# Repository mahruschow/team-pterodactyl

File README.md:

# Team PTERODACTYL

Working files for the UMD near-space PTERODACTYL sensor-board redesign. The current board is an imported **v3.8 v11 baseline**, not a completed next-launch design or a fabrication release.

## Team handoff and planning

For a quick picture of progress and what's left, read [docs/REMAINING_WORK.md](docs/REMAINING_WORK.md). Start with [docs/README.md](docs/README.md) for the shared planning directory, then [current status and resume steps](docs/CURRENT_STATUS.md). The directory includes requirements, the development plan, session notes, the supplied parts workbook and native KiCad validation evidence so teammates can continue without the previous chat.

Step 3 now includes a project-local `Pterodactyl_Modules` library with draft BNO055 #2472/MS8607 #4716 carrier footprints with matching symbols, a Teensy SSW carrier, and an unassigned GPS #5440 logical symbol, plus documented connector/mounting proposals. They are not assigned to the main circuit. See [the footprint review](docs/FOOTPRINT_REVIEW.md) for pin mapping, validation and outstanding physical-fit requirements.

Step 5 adds a separate **draft v4 schematic** in `Native_KiCad_v4/`, built from the documented connection map and power architecture. It passes ERC with 0 violations and matches an independent net list, but it is not yet team-reviewed. Step 7 adds a placed (not yet routed) v4 PCB in the same project; see [the draft layout](docs/PCB_LAYOUT_V4.md). See [the power architecture and schematic plan](docs/POWER_ARCHITECTURE.md).

## Open the design

Use KiCad 10 to open `Native_KiCad_v11/PTERODACTYL_v3.8_v11.kicad_pro`. The project contains a native KiCad schematic, PCB, imported symbol and footprint libraries, and project-local library tables. These files were converted from the supplied Autodesk Fusion/Eagle source; component choices and connectivity still need engineering review.

| Folder or file | Purpose |
|---|---|
| `Native_KiCad_v11/` | Editable KiCad project and the saved October 7, 2026 PCB DRC report |
| `Native_KiCad_v4/` | Draft v4 project: schematic (Step 5) and placed, unrouted PCB (Step 7); see docs/PCB_LAYOUT_V4.md |
| `KiCad_import/` | Eagle XML schematic and board pair prepared for KiCad's Eagle importer |
| `Original_Fusion_source/` | Supplied editable `.f3z`, `.sch`, and `.brd` files for comparison |
| `Firmware_v4/` | Draft v4 logger firmware (Step 6); compiles for Teensy 4.1, not yet hardware-tested |
| `Firmware_reference/` | Original v19 and v19.1 firmware archives from the supplied package; not validated for this redesign |
| `Reference_Gerbers_v12_DO_NOT_ORDER/` | Historical Gerbers for revision comparison only |
| `PTERODACTYL_V3.8_Setup_reference.pdf` | Original setup guide from the supplied package |
| `CUSTOM_BOARD_BRIEF.md` | Sensor goals and decisions still to make |

## Current state

The imported PCB has approximately 97.79 × 97.79 mm outer dimensions, four copper layers, 39 footprints, 417 tracks, and two refilled copper zones. It uses a Teensy 4.1 baseline. A fresh KiCad 10.0.7 audit on October 18, 2026 reproduced **11 PCB DRC errors, 428 warnings, and 0 unconnected items**. Schematic ERC reported **33 errors and 10 warnings**, with **52 additional schematic/PCB parity warnings**. These findings remain unresolved. See the [validation report](docs/validation/2026-10-18/VALIDATION_SUMMARY.md) for triage and check limitations, and the [development plan](docs/DEVELOPMENT_PLAN.md) for next steps. The symbols, pin mapping, power architecture and exact module footprints still require engineering review.

The supplied Gerbers say v3.8 **v12** while the editable Fusion source says v3.8 **v11**; the Gerber job metadata also contains a v3.7 identifier. Reconcile those revisions before using any prior files for fabrication.

## Next-launch work

The intended board should log gyroscope, accelerometer, orientation, GPS, pressure, humidity, temperature, and derived altitude data. The working selection is Teensy 4.1 with Adafruit BNO055 2472, MS8607 4716 and PA1616D GPS 5440. The lead has specified no telemetry: record onboard to microSD for analysis after recovery. Saadat selected the core logger with power control, status LEDs and supply monitoring; OLED, remote probes, alternative IMU, heater and servos are outside this scope. Component placement must address interference. Battery/runtime, quantitative performance, enclosure/environment, exact control workflow and manufacturer constraints remain open. See `CUSTOM_BOARD_BRIEF.md` and the [version-one requirements draft](docs/V1_REQUIREMENTS.md), which distinguishes the selected baseline from proposed behavior and open decisions.

Before fabrication: agree on the requirements and reference revision; review the schematic and all footprints against component datasheets; check power, pin mapping, routing, and board dimensions; resolve DRC/ERC failures; generate fresh Gerbers and drill files from the approved KiCad board; inspect them in a Gerber viewer; and obtain a hardware review and prototype test.

## Collaborating

Clone this private repository, open the `.kicad_pro` file, and commit changes on a branch. Keep the KiCad project, schematic, PCB, and local libraries together. Do not commit editor lock files or local UI settings. Explain changes to connectors, sensors, pin mapping, and power in the commit or pull request so they can be checked against the schematic and firmware.

**Do not send the reference Gerbers or this imported baseline directly to a manufacturer.**

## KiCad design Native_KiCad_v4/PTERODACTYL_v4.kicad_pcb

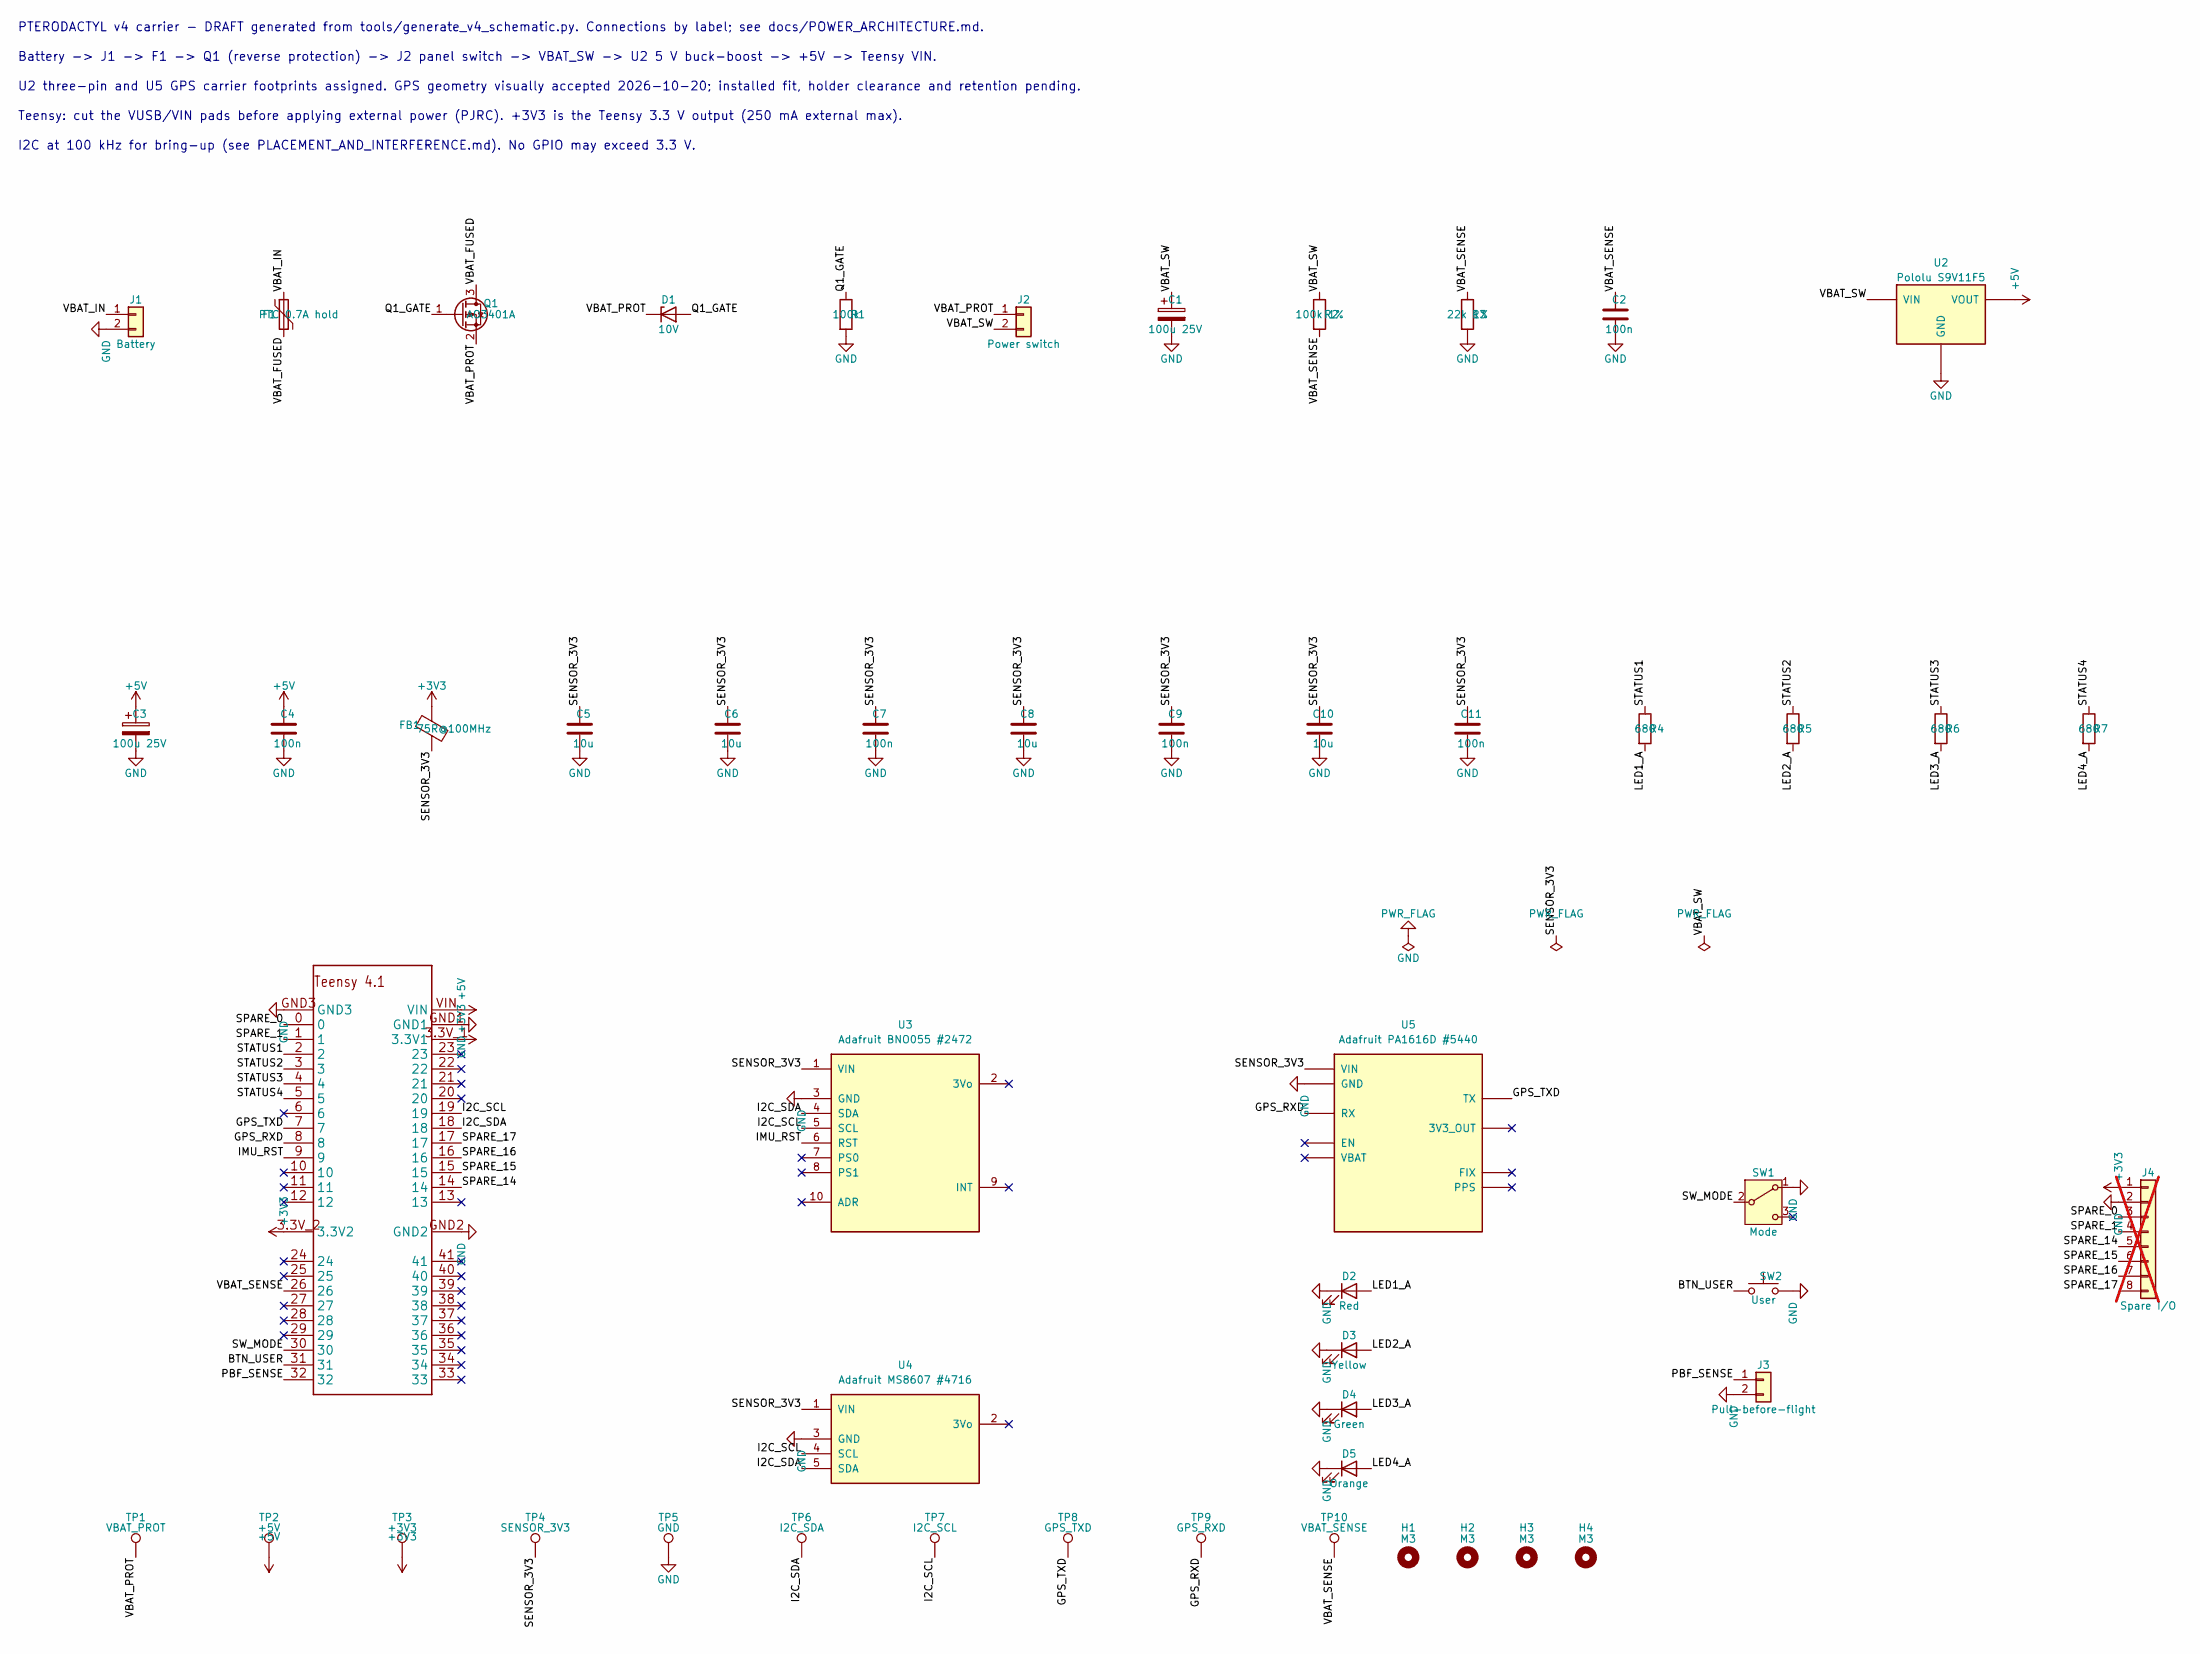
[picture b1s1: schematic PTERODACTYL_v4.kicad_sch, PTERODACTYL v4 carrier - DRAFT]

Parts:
C1, C3: 100u 25V; Panasonic_EEUFR1E101_P2.50mm; MPN EEUFR1E101
C2, C4, C7, C9, C11: 100n; KEMET_C322_100n_P5.00mm; MPN C322C104K5R5TA
C5, C6, C8, C10: 10u; KEMET_C322_10u_P5.00mm; MPN C322C106K3R5TA
D1: 10V; D_DO-35_SOD27_P7.62mm_Horizontal; MPN BZX79-C10,133
D2: Red; LED_D5.0mm; MPN WP7113LID
D3: Yellow; LED_D5.0mm; MPN WP7113LYD
D4: Green; LED_D5.0mm; MPN WP7113LGD
D5: Orange; LED_D5.0mm; MPN WP7113LSECK/J4
F1: PTC 0.7A hold; Fuse_Bourns_MF-RHT070; MPN MF-RHT070-0
FB1: 75R@100MHz; Laird_28L0138_P10.00mm; MPN 28L0138-10R-10
H1, H2, H3, H4: M3; MountingHole_3.2mm_M3
J1: Battery; Molex_0022272021_AISLER; MPN 0022272021
J2: Power switch; Molex_0022272021_AISLER; MPN 0022272021
J3: Pull-before-flight; PinHeader_1x02_P2.54mm_Vertical; MPN HTSW-102-07-T-S
J4: Spare I/O; PinHeader_1x08_P2.54mm_Vertical; MPN DNP; not fitted
Q1: AO3401A; AO3401A_SOT23_AISLER; MPN AO3401A
R1: 100k; Vishay_MRS16_P7.62mm; MPN MRS16000C1003FCT00
R2: 100k 1%; Vishay_MRS16_P7.62mm; MPN MRS16000C1003FCT00
R3: 22k 1%; Vishay_MRS16_P7.62mm; MPN MRS16000C2202FCT00
R4, R5, R6, R7: 680; Vishay_MRS16_P7.62mm; MPN MRS16000C6800FCT00
SW1: Mode; SW_Slide_SPDT_Straight_CK_OS102011MS2Q; MPN OS102011MS2QN1
SW2: User; SW_PUSH_6mm; MPN PTS645SL50-2 LFS
TP1: VBAT_PROT; TestPoint_THTPad_D2.0mm_Drill1.0mm; MPN PCB PAD ONLY
TP2: +5V; TestPoint_THTPad_D2.0mm_Drill1.0mm; MPN PCB PAD ONLY
TP3: +3V3; TestPoint_THTPad_D2.0mm_Drill1.0mm; MPN PCB PAD ONLY
TP4: SENSOR_3V3; TestPoint_THTPad_D2.0mm_Drill1.0mm; MPN PCB PAD ONLY
TP5: GND; TestPoint_THTPad_D2.0mm_Drill1.0mm; MPN PCB PAD ONLY
TP6: I2C_SDA; TestPoint_THTPad_D2.0mm_Drill1.0mm; MPN PCB PAD ONLY
TP7: I2C_SCL; TestPoint_THTPad_D2.0mm_Drill1.0mm; MPN PCB PAD ONLY
TP8: GPS_TXD; TestPoint_THTPad_D2.0mm_Drill1.0mm; MPN PCB PAD ONLY
TP9: GPS_RXD; TestPoint_THTPad_D2.0mm_Drill1.0mm; MPN PCB PAD ONLY
TP10: VBAT_SENSE; TestPoint_THTPad_D2.0mm_Drill1.0mm; MPN PCB PAD ONLY
U1: Teensy 4.1; Teensy41_SSW_Carrier; MPN PJRC Teensy 4.1
U2: Pololu S9V11F5; Pololu_S9V11F5_SSW_Carrier; MPN Pololu #2836
U3: Adafruit BNO055 #2472; Adafruit_BNO055_2472_Carrier; MPN Adafruit 2472
U4: Adafruit MS8607 #4716; Adafruit_MS8607_4716_Carrier; MPN Adafruit 4716
U5: Adafruit PA1616D #5440; Adafruit_GPS_5440_Carrier; MPN Adafruit 5440

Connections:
+3V3: FB1.1, J4.1, TP3.1, U1.3.3V_1 (3.3V1), U1.3.3V_2 (3.3V2)
+5V: C3.1, C4.1, TP2.1, U1.VIN, U2.VOUT
/BTN_USER: SW2.1, U1.31
/GPS_RXD: TP9.1, U1.8, U5.RX
/GPS_TXD: TP8.1, U1.7, U5.TX
/I2C_SCL: TP7.1, U1.19, U3.5 (SCL), U4.4 (SCL)
/I2C_SDA: TP6.1, U1.18, U3.4 (SDA), U4.5 (SDA)
/IMU_RST: U1.9, U3.6 (RST)
/LED1_A: D2.2 (A), R4.2
/LED2_A: D3.2 (A), R5.2
/LED3_A: D4.2 (A), R6.2
/LED4_A: D5.2 (A), R7.2
/PBF_SENSE: J3.1, U1.32
/Q1_GATE: D1.2 (A), Q1.1 (G), R1.1
/SENSOR_3V3: C5.1, C6.1, C7.1, C8.1, C9.1, C10.1, C11.1, FB1.2, TP4.1, U3.1 (VIN), U4.1 (VIN), U5.VIN
/SPARE_0: J4.3, U1.0
/SPARE_1: J4.4, U1.1
/SPARE_14: J4.5, U1.14
/SPARE_15: J4.6, U1.15
/SPARE_16: J4.7, U1.16
/SPARE_17: J4.8, U1.17
/STATUS1: R4.1, U1.2
/STATUS2: R5.1, U1.3
/STATUS3: R6.1, U1.4
/STATUS4: R7.1, U1.5
/SW_MODE: SW1.2 (B), U1.30
/VBAT_FUSED: F1.2, Q1.3 (D)
/VBAT_IN: F1.1, J1.1
/VBAT_PROT: D1.1 (K), J2.1, Q1.2 (S), TP1.1
/VBAT_SENSE: C2.1, R2.2, R3.1, TP10.1, U1.26
/VBAT_SW: C1.1, J2.2, R2.1, U2.VIN
GND: C1.2, C2.2, C3.2, C4.2, C5.2, C6.2, C7.2, C8.2, C9.2, C10.2, C11.2, D2.1 (K), D3.1 (K), D4.1 (K), D5.1 (K), J1.2, J3.2, J4.2, R1.2, R3.2, SW1.1 (A), SW2.2, TP5.1, U1.GND1, U1.GND2, U1.GND3, U2.GND, U3.3 (GND), U4.3 (GND), U5.GND

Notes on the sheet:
PTERODACTYL v4 carrier - DRAFT generated from tools/generate_v4_schematic.py. Connections by label; see docs/POWER_ARCHITECTURE.md.
Battery -> J1 -> F1 -> Q1 (reverse protection) -> J2 panel switch -> VBAT_SW -> U2 5 V buck-boost -> +5V -> Teensy VIN.
U2 three-pin and U5 GPS carrier footprints assigned. GPS geometry visually accepted 2026-10-20; installed fit, holder clearance and retention pending.
Teensy: cut the VUSB/VIN pads before applying external power (PJRC). +3V3 is the Teensy 3.3 V output (250 mA external max).
I2C at 100 kHz for bring-up (see PLACEMENT_AND_INTERFERENCE.md). No GPIO may exceed 3.3 V.

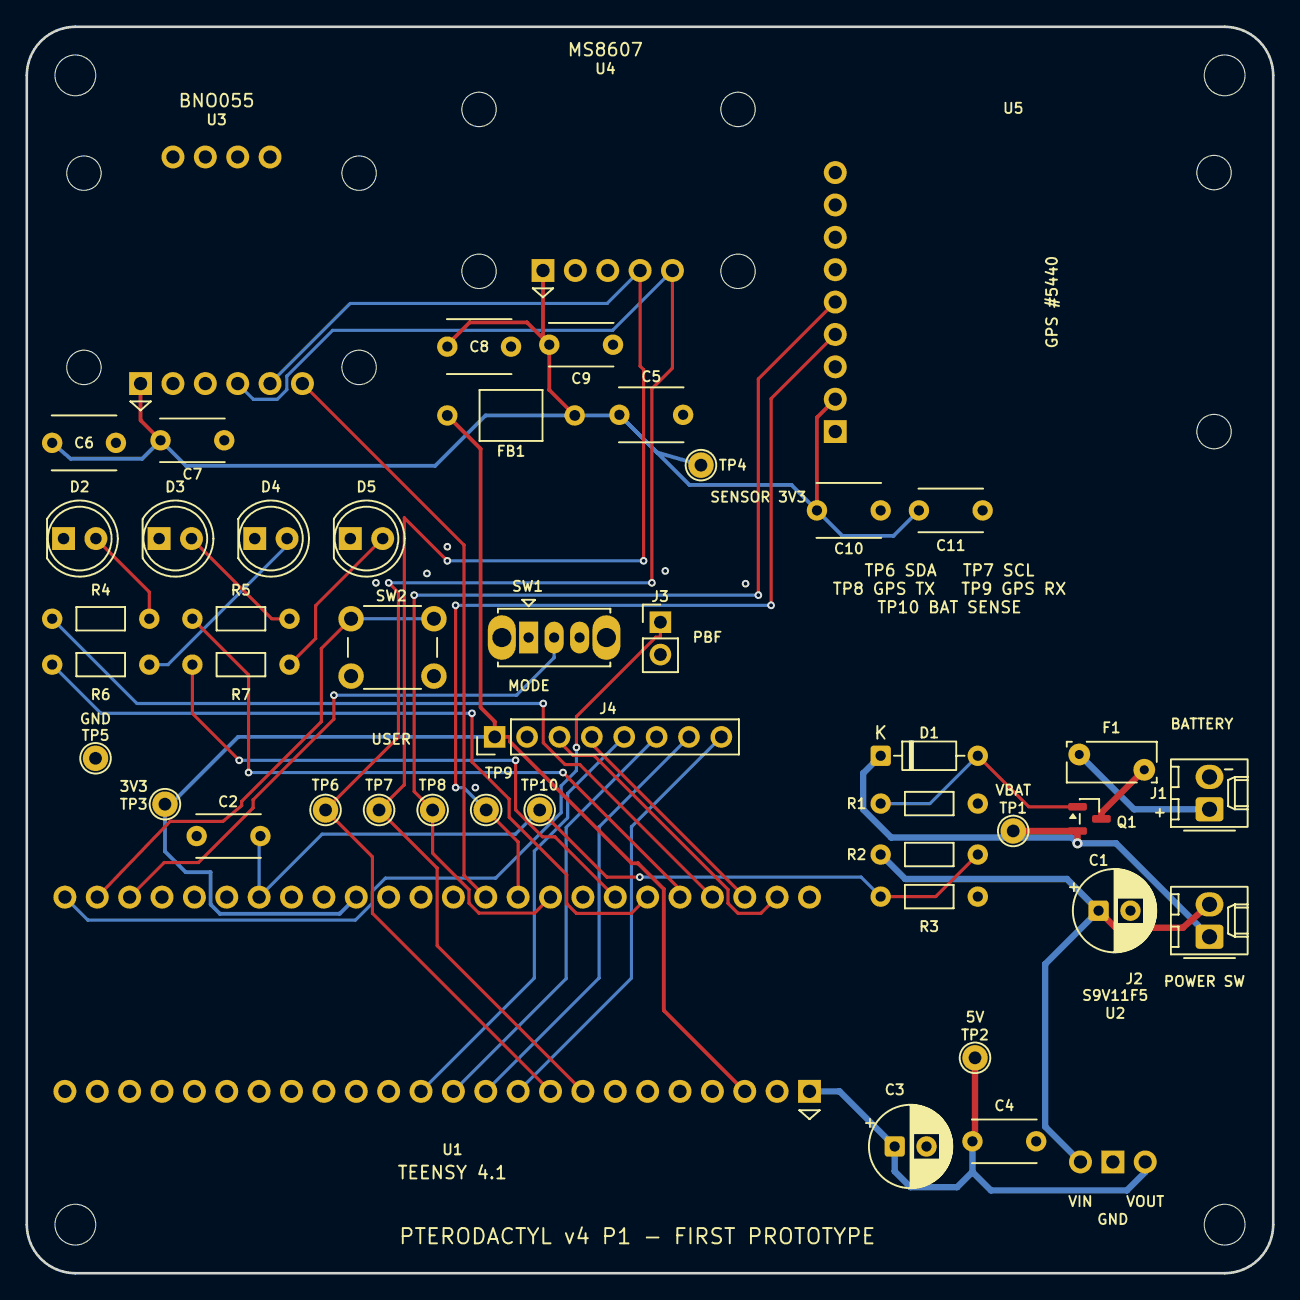
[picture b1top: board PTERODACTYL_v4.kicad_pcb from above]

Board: 4 copper layers, 97.8 x 97.8 mm, 51 parts (0 on the bottom side), 32 nets.

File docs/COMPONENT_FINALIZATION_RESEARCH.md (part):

# Component finalization research — handoff October 21, 2026

## Team-name silkscreen update — October 21, 2026

Saadat Muyeen, Mahrus Chowdhury and Ryeed Zaman are now on the back silkscreen, with 2 mm text and 0.30 mm strokes. Fresh DRC, connectivity and schematic-parity checks report zero issues. All original PCB bytes are retained; only three text objects were added. The other eight Gerber layers match the prior geometry exactly, apart from export timestamps. Existing ERC evidence remains applicable to the unchanged schematic.

**Order the updated native PCB or fabrication ZIP. AISLER TCVOYNZG revision 1 is superseded and does not contain the names.** Two revision-upload attempts failed; the alternate upload form says an anonymous project is already in progress and requires login to save it. Sign in and upload the updated board, then inspect the bottom preview before ordering. No new AISLER revision or order has been created. Earlier statements below about revision 1 being the exact current PCB or ready for checkout refer to the previous checkpoint.

## First prototype scope and order checkpoint - October 21, 2026

**Current authority: [FIRST_PROTOTYPE_RELEASE.md](FIRST_PROTOTYPE_RELEASE.md).** PCB checks and AISLER upload/preview passed; project TCVOYNZG revision 1 is ready for checkout. FB1/SW1/SW2/J3 are selected for P1. The user explicitly excludes physical testing, flight qualification, subsequent redesign and casing from this phase; older statements requiring those before PCB fabrication are superseded. Assembly receipt/polarity checks remain part of building the prototype. No order placed. Updated known cost is USD 129.37 (15 price lines missing); entered mass 170.25 g (three missing). The provisional EUR board quote is separate.

**Historical research checkpoint, not a released BOM.** The later targeted implementation and revised choices (including MRS16 and BH4AAW) are in [COMPONENT_IMPLEMENTATION.md](COMPONENT_IMPLEMENTATION.md). Statements below about changes not being applied describe the earlier checkpoint.

**Original research boundary:** These recommendations have not been applied to the schematic, PCB, exported BOM or live budget. The current native design still contains the earlier candidate/generic components. See RESUME_HERE.md for authoritative requirements and next actions. No purchase or new native-design validation occurred during this research.

## Battery and storage recommendations

**Battery: four Energizer L91 AA Li/FeS2 primary cells in series**, nominal 6 V, typical cell-only mass 60 g. This is the leading lightweight candidate for the existing buck-boost architecture, not a guarantee of three-hour operation. Its published operating range includes -40 C. Four cells reduce required current and improve startup voltage margin relative to three; series connection does not multiply Ah. These are non-rechargeable cells. [Energizer current datasheet](https://data.energizer.com/pdfs/L91GL0225.pdf).

The manufacturer's temperature graph was visually inspected: capacity falls strongly at -40 C under higher loads. The 2.5 A continuous headline is single-cell data at room temperature unless otherwise stated; do not apply it unchanged at -40 C. Do not assign a fixed 3.5 Ah cold capacity from the room-temperature curve. Existing model currents for a four-cell pack are approximately 0.249 A average / 0.547 A peak at 6 V, and 0.374 A / 0.821 A at 4 V. Four volts is a screening example, not an implemented cutoff. The regulator needs at least 3 V at its own input to start, after wiring/protection losses. Select a qualified loaded-voltage endpoint and test cold startup and complete logging.

The **holder/finished pack is unresolved**. MPD BA4AAW's manufacturer drawing specifies -10 to +100 C, so it is not an acceptable rated -40 C choice. MPD 6S-AA is rated -40 to +180 C but holds only ONE cell and uses PCB pins; four of them would need additional integration. Do not misidentify it as a four-cell holder. A professionally assembled pack is another option, but no pack-builder SKU has been verified. Cell restraint, wiring and connector mass must be added to the 60 g cells. Sources: [BA4AAW drawing](https://www.batteryholders.com/uploads/parts/BA4AAW/datashee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, [MPD 6S-AA](https://products.memoryprotectiondevices.com/?page_id=793).

**microSD: Kingston Industrial SDCIT2/8GB**, 8 GB pSLC industrial microSDHC, -40 to +85 C; FAT32 for the initial Teensy logging setup. SDCIT2/8GBSP is the no-adapter variant; the adapter is not flown. Eight GB leaves ample space for this logger. The public summary does not establish an exact current maximum; measure write/startup peaks and retain an explicitly provisional allowance. Card power-failure features do not replace firmware sync/clean-stop handling. [Kingston datasheet](https://www.kingston.com/datasheets/SDCIT2_en.pdf), [exact product](https://www.kingston.com/en/memory/search?partid=SDCIT2%2F8GB).

## On-board component research

The table records the proposed order code and remaining review, not permission to silently substitute other parts. Quantities derive from the current schematic.

| References | Proposed exact part | Findings / remaining work |
| --- | --- | --- |
| U1–U5 | PJRC Teensy 4.1; Pololu 2836; Adafruit 2472, 4716, 5440 | Retain specified modules. Whole-module cold operation is not established merely from individual IC ratings. |
| C1, C3 | Panasonic **EEUFR1E101**, 100 uF 25 V | Proposed C1 increase from 47 to 100 uF and C3 voltage increase from 10 to 25 V. 6.3 mm diameter, 11.2 mm body length, 2.5 mm pitch, -40 to +105 C. Existing radial footprint matches nominal pitch/diameter; height and cold impedance still need review. |
| C2, C4, C7, C9, C11 | KEMET **C322C104K5R5TA**, 100 nF 50 V 10% X7R | Max body 5.08 mm long, 3.18 mm thick, 6.6 mm high. Generic disc body is inaccurate. |
| C5, C6, C8, C10 | KEMET **C322C106K3R5TA**, 10 uF 25 V 10% X7R | Max body 5.08 mm long, 4.07 mm thick, 6.6 mm high. Generic disc body is inaccurate. Review usable capacitance under bias and temperature. |
| Q1 | Alpha & Omega **AO3401A** | Candidate replacement for discontinued IRLML6402. SOT-23 G/S/D, top-view drawing inspected. -30 V Vds, +/-12 V Vgs, max 85 mOhm at -2.5 V gate drive. Check pin mapping against existing G1/S2/D3 and source-to-protected-rail orientation. No replacement applied yet. |
| D1 | Nexperia **BZX79-C10,133** | 10 V zener, DO-35. Existing R1 gives low clamp bias; do not claim precise 10 V clamping at arbitrary input voltage. Four-cell battery contract is narrower than regulator's standalone 16 V input limit. |
| F1 | Bourns **MF-RHT070-0** | 0.7 A hold / 1.4 A trip nominal at 23 C. Hold changes with temperature (about 0.95 A at -40 C, 0.62 A at 40 C). Review time-current curve, path loss, startup and fault behavior; hold is not an instantaneous cutoff. Retain as candidate until reviewed. |
| FB1 | Murata **BL01RN1A2A2B** | Bulk packaging suffix B; source family drawing matches existing axial footprint. Confirm exact current, temperature and ordering status from manufacturer documentation before closing. |
| R1, R2 | Vishay **MRS25000C1003FCT00** | 100 kOhm, 1%. Check active ordering status and maximum body dimensions against DIN0207 footprint. |
| R3 | Vishay **MRS25000C2202FCT00** | 22 kOhm, 1%. Same family review. |
| R4–R7 | Vishay **MRS25000C6800FCT00** | 680 Ohm, 1%. Retain resistance. |
| D2 | Kingbright **WP7113LID** | Low-current red, 5 mm THT. |
| D3 | Kingbright **WP7113LYD** | Low-current yellow, 5 mm THT. |
| D4 | Kingbright **WP7113LGD** | Low-forward-voltage green, 5 mm THT; avoid a generic high-Vf green substitution. |
| D5 | Kingbright **WP7113LSECK/J4** | Low-current orange, 5 mm THT. Check flange/body limits and recalculate actual LED current assumptions. |
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
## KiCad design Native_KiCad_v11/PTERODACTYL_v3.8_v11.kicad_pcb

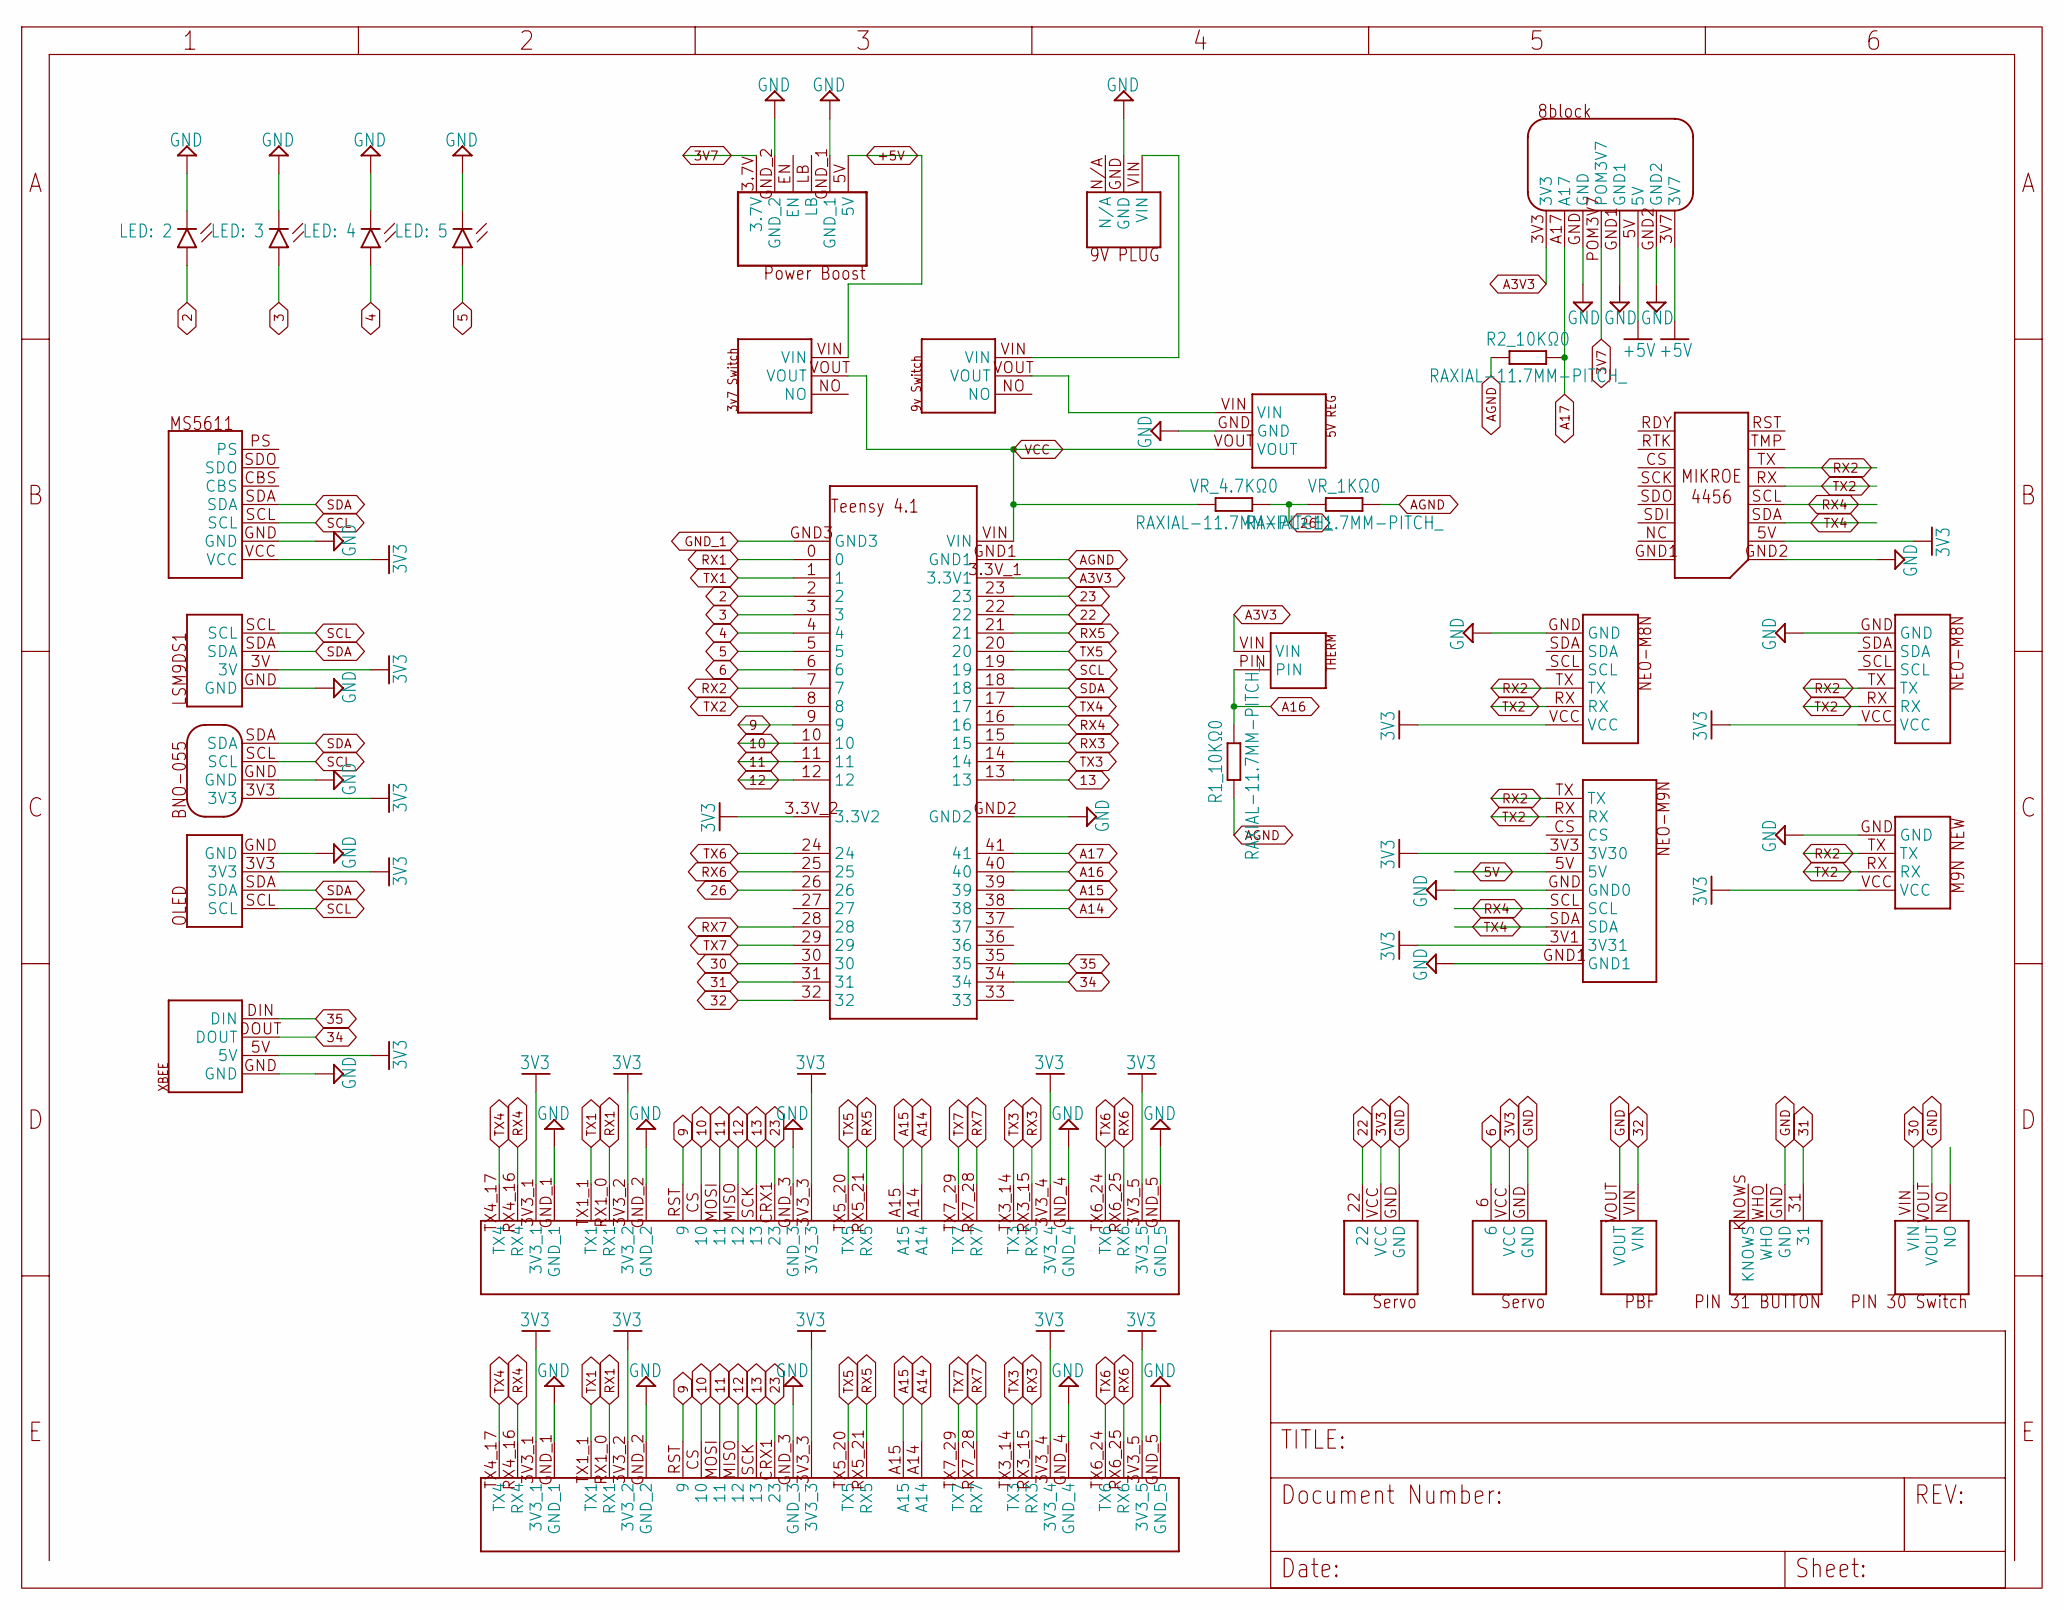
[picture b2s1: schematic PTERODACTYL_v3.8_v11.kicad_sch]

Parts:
D1: LED: 3; LEDRD254W60D565H860B_W
D2: LED: 4; LEDRD254W60D565H860B
D3: LED: 5; LEDRD254W60D565H860B_B
D4: LED: 2; LEDRD254W60D565H860B_Y
R1_10KΩ0, R2_10KΩ0: RAXIAL-11.7MM-PITCH_; RESAD1176W63L850D250B
U$1: FEMALE_HEADERS_V1.3
U$2: TERMINAL_BLOCK_V1.3
U$3: TEENSY41_SIMPLE
U$4: PT8BLOCK; PTERODACTYL8BLOCK
U$5: 5VREG
U$6: 3V7SWITCH
U$7: 9VSWITCH
U$8: 9VPLUG
U$9: OLED_SIMPLE
U$10: LSM9DS1_SIMPLE
U$11: MS5611
U$12: UBLOXM8NTERMINAL
U$13: UBLOXM8NSIMPLE
U$14: XBEE_SIMPLE
U$15: UBLOXM9NSIMPLE
U$16: THERMISTOR10K1; THERMISTOR10K
U$17: BNO055
U$22: UBLOXM9N_NEW_SIMPLE
U$23: SERVO; PIN6SERVO
U$24: PBF; PULLBEFOREFLIGHT
U$25: BUTTON; PIN31BUTTON
U$26: PIN30SWITCH
U$27: SERVO22; PI22SERVO
U$28: POWERBOOST; 5VPOWERBOOST
U$29: MIKROE
VR_1KΩ0, VR_4.7KΩ0: RAXIAL-11.7MM-PITCH_; RESAD1176W63L850D250B

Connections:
2: D4.1 (A), U$3.2
3: D1.1 (A), U$3.3
3V3: U$1.3V3_1, U$1.3V3_2, U$1.3V3_3, U$1.3V3_4, U$1.3V3_5, U$2.3V3_1, U$2.3V3_2, U$2.3V3_3, U$2.3V3_4, U$2.3V3_5, U$3.3.3V_2 (3.3V2), U$9.3V3, U$10.3V, U$11.VCC, U$12.VCC, U$13.VCC, U$14.5V, U$15.3V1 (3V31), U$15.3V3 (3V30), U$17.3V3, U$22.VCC, U$23.VCC, U$27.VCC, U$29.5V
3V7: U$4.POM3V7, U$28.3.7V
4: D2.1 (A), U$3.4
5: D3.1 (A), U$3.5
5V: U$15.5V
6: U$3.6, U$23.6
9: U$1.RST (9), U$2.RST (9), U$3.9
10: U$1.CS (10), U$2.CS (10), U$3.10
11: U$1.MOSI (11), U$2.MOSI (11), U$3.11
12: U$1.MISO (12), U$2.MISO (12), U$3.12
13: U$1.SCK (13), U$2.SCK (13), U$3.13
22: U$3.22, U$27.22
23: U$1.CRX1 (23), U$2.CRX1 (23), U$3.23
26: U$3.26, VR_1KΩ0.1, VR_4.7KΩ0.2
30: U$3.30, U$26.VIN
31: U$3.31, U$25.31
32: U$3.32, U$24.VIN
34: U$3.34, U$14.DOUT
35: U$3.35, U$14.DIN
+5V: U$4.3V7, U$4.5V, U$6.VIN, U$28.5V
A3V3: U$3.3.3V_1 (3.3V1), U$4.3V3, U$16.VIN
A14: U$1.A14, U$2.A14, U$3.38
A15: U$1.A15, U$2.A15, U$3.39
A16: R1_10KΩ0.2, U$3.40, U$16.PIN
A17: R2_10KΩ0.2, U$3.41, U$4.A17
AGND: R1_10KΩ0.1, R2_10KΩ0.1, U$3.GND1, VR_1KΩ0.2
GND: D1.2 (C), D2.2 (C), D3.2 (C), D4.2 (C), U$1.GND_1, U$1.GND_2, U$1.GND_3, U$1.GND_4, U$1.GND_5, U$2.GND_1, U$2.GND_2, U$2.GND_3, U$2.GND_4, U$2.GND_5, U$3.GND2, U$4.GND, U$4.GND1, U$4.GND2, U$5.GND, U$8.GND, U$9.GND, U$10.GND, U$11.GND, U$12.GND, U$13.GND, U$14.GND, U$15.GND (GND0), U$15.GND1, U$17.GND, U$22.GND, U$23.GND, U$24.VOUT, U$25.GND, U$26.VOUT, U$27.GND, U$28.GND_1, U$28.GND_2, U$29.GND2
GND_1: U$3.GND3
RX1: U$1.RX1_0 (RX1), U$2.RX1_0 (RX1), U$3.0
RX2: U$3.7, U$12.TX, U$13.TX, U$15.TX, U$22.TX, U$29.TX
RX3: U$1.RX3_15 (RX3), U$2.RX3_15 (RX3), U$3.15
RX4: U$1.RX4_16 (RX4), U$2.RX4_16 (RX4), U$3.16, U$15.SCL, U$29.SCL
RX5: U$1.RX5_21 (RX5), U$2.RX5_21 (RX5), U$3.21
RX6: U$1.RX6_25 (RX6), U$2.RX6_25 (RX6), U$3.25
RX7: U$1.RX7_28 (RX7), U$2.RX7_28 (RX7), U$3.28
SCL: U$3.19, U$9.SCL, U$10.SCL, U$11.SCL, U$17.SCL
SDA: U$3.18, U$9.SDA, U$10.SDA, U$11.SDA, U$17.SDA
TX1: U$1.TX1_1 (TX1), U$2.TX1_1 (TX1), U$3.1
TX2: U$3.8, U$12.RX, U$13.RX, U$15.RX, U$22.RX, U$29.RX
TX3: U$1.TX3_14 (TX3), U$2.TX3_14 (TX3), U$3.14
TX4: U$1.TX4_17 (TX4), U$2.TX4_17 (TX4), U$3.17, U$15.SDA, U$29.SDA
TX5: U$1.TX5_20 (TX5), U$2.TX5_20 (TX5), U$3.20
TX6: U$1.TX6_24 (TX6), U$2.TX6_24 (TX6), U$3.24
TX7: U$1.TX7_29 (TX7), U$2.TX7_29 (TX7), U$3.29
VCC: U$3.VIN, U$5.VOUT, U$6.VOUT, VR_4.7KΩ0.1
VCC_2: U$7.VIN, U$8.VIN
VCC_3: U$5.VIN, U$7.VOUT

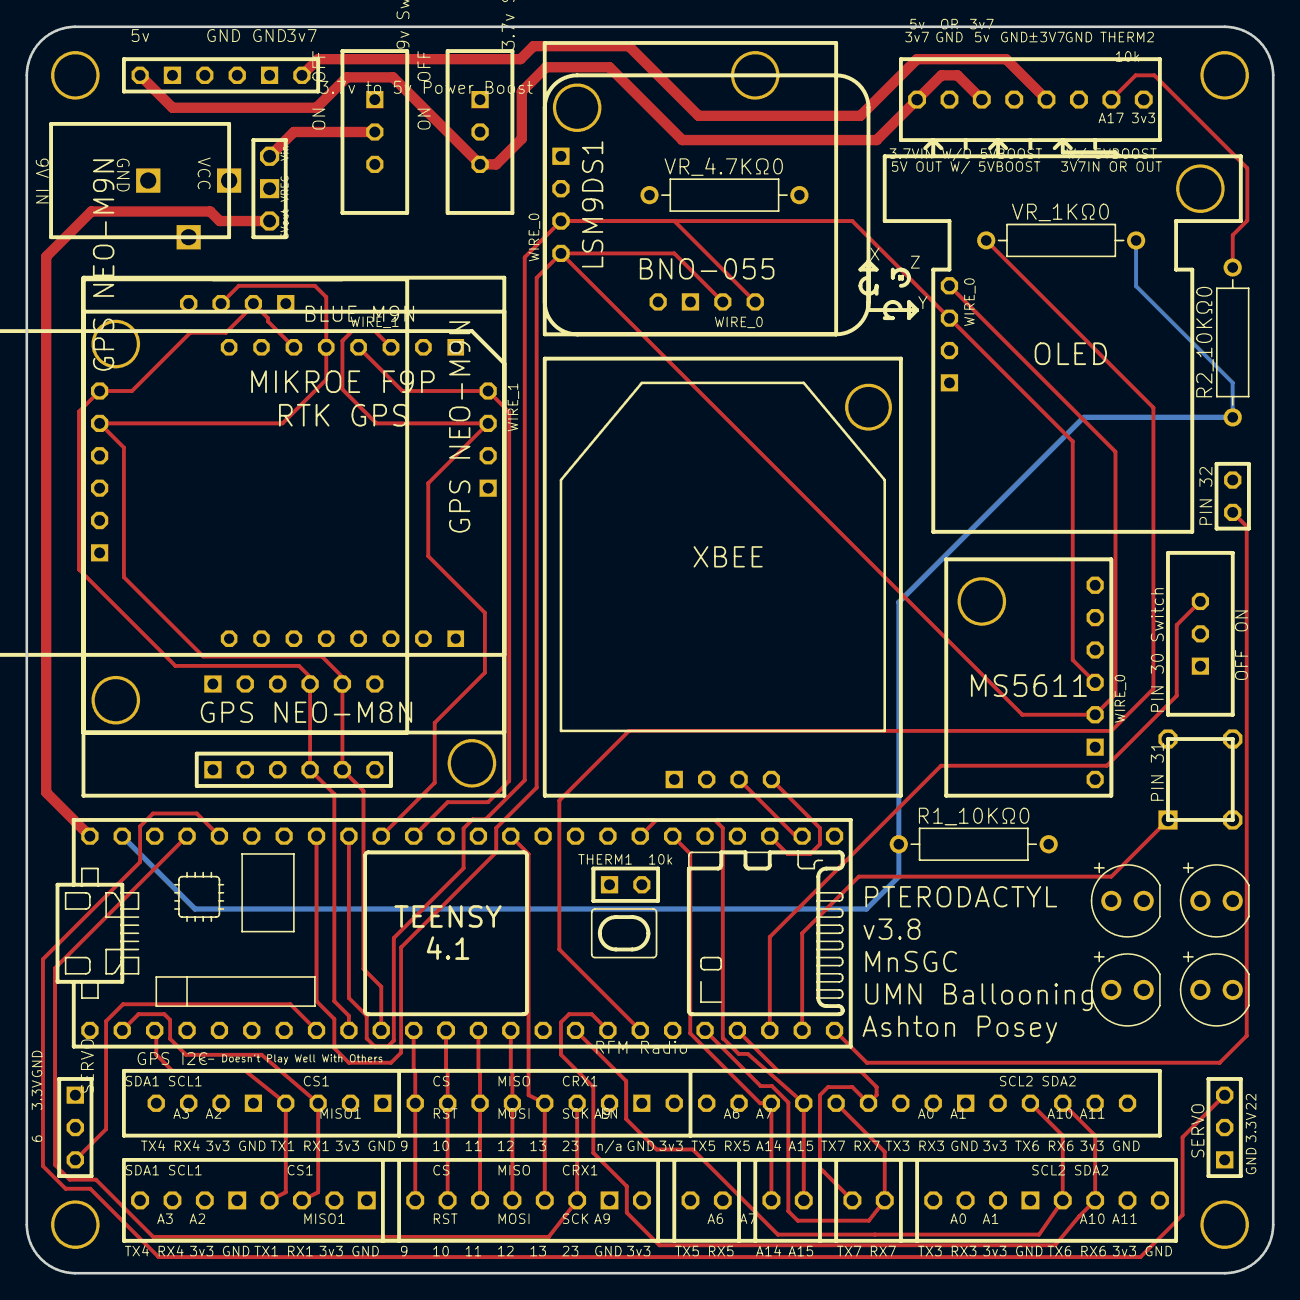
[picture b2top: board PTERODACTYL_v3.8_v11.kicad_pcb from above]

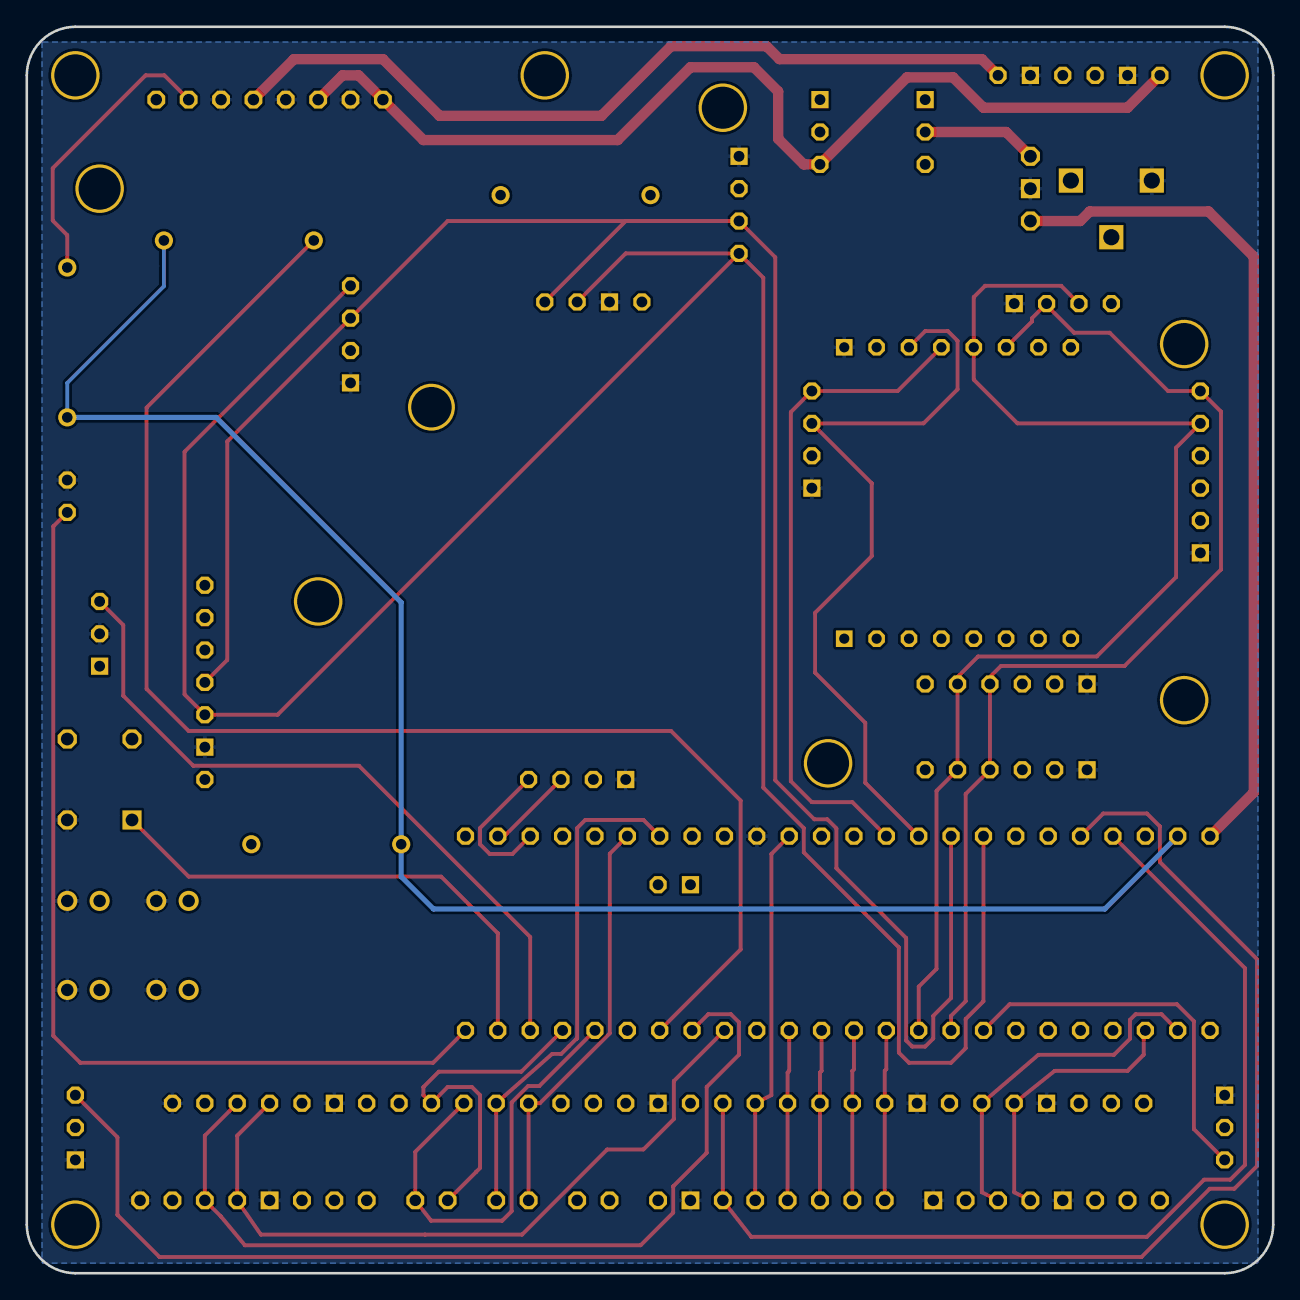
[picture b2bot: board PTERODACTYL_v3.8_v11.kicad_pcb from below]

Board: 4 copper layers, 97.8 x 97.8 mm, 39 parts (4 on the bottom side), 47 nets.

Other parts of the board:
U$18, U$19, U$20, U$21: HOLE
U$30: PTERODACTYLV3.1
U$32: AXIS

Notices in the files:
parts and their libraries:
Adafruit 5440 carrier; legacy PA6H CAD 70430c1 geometry visually accepted by Saadat 2026-10-20. Physical fit/holder clearance pending. CC BY-SA 3.0, Adafruit Industries/Limor Fried.
